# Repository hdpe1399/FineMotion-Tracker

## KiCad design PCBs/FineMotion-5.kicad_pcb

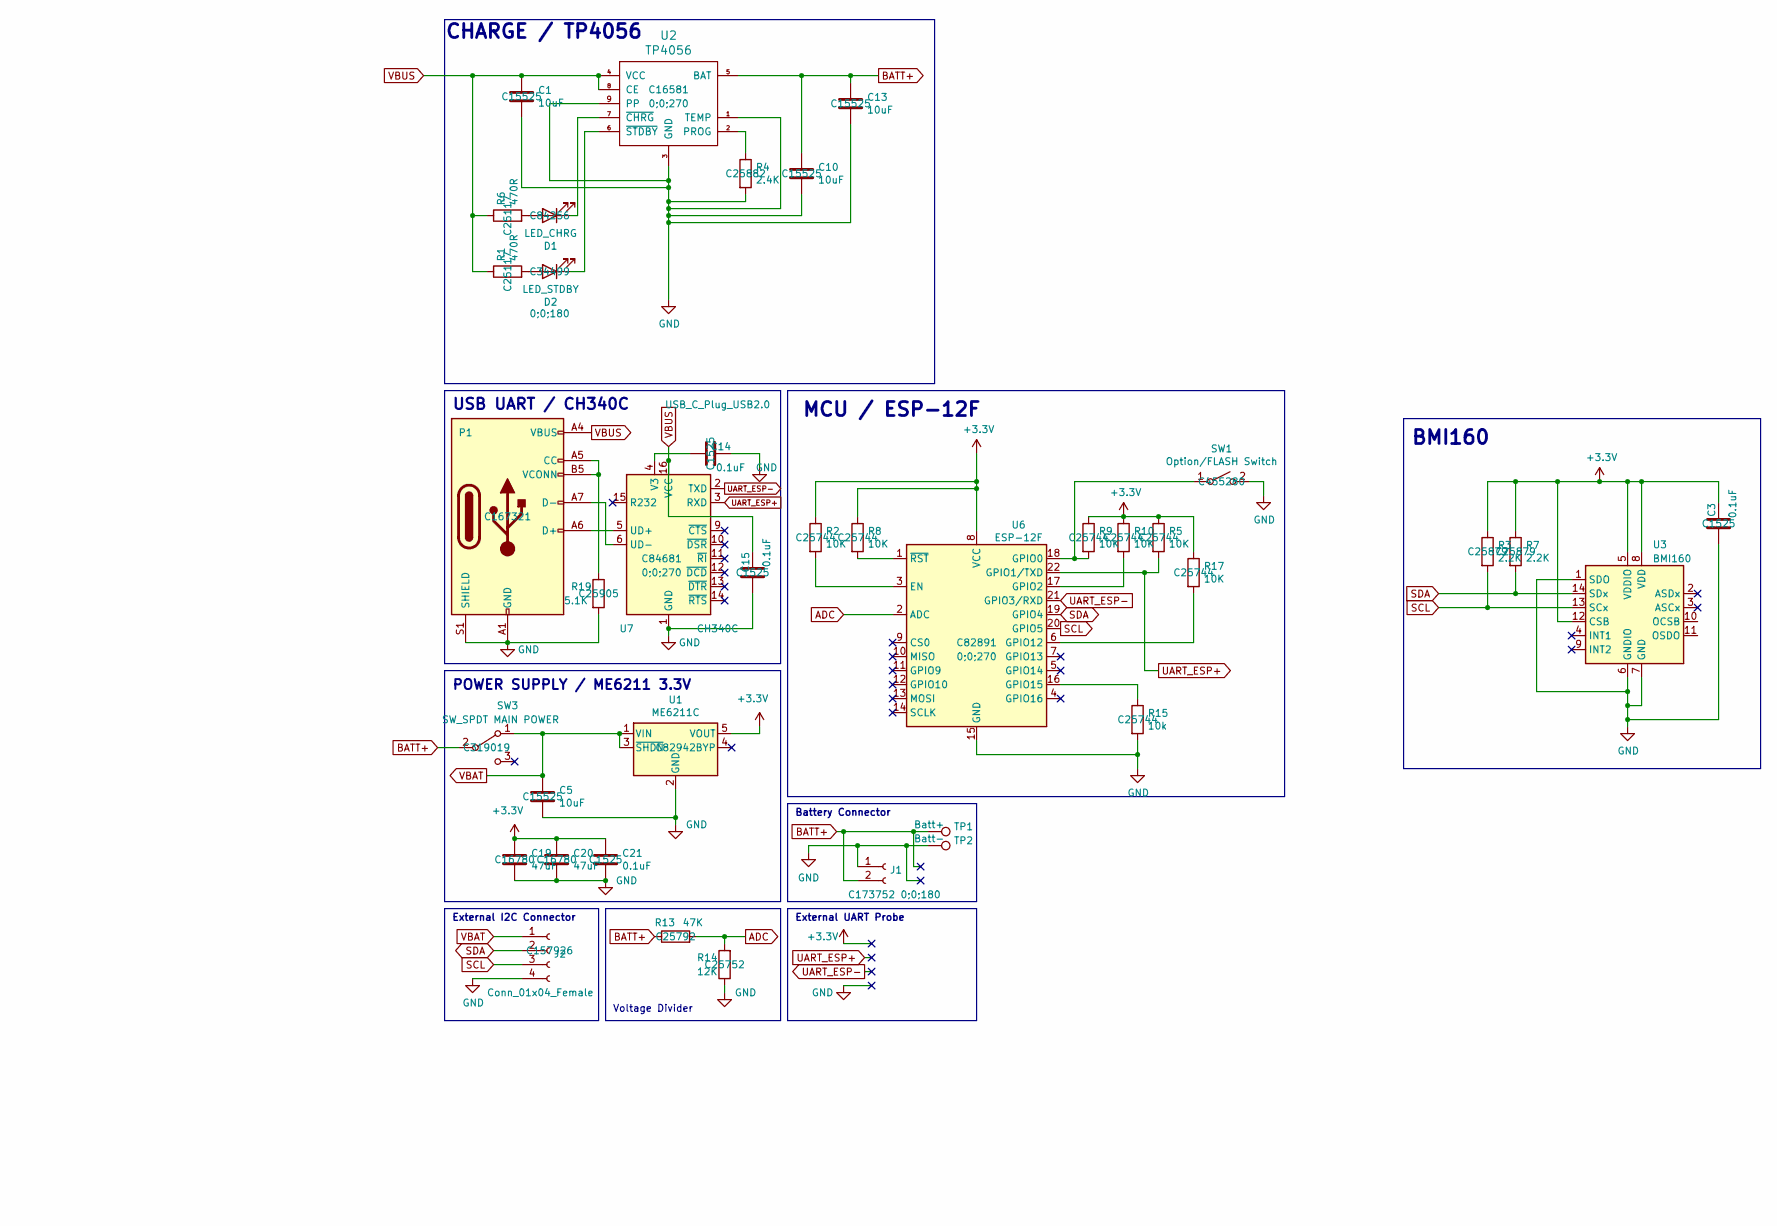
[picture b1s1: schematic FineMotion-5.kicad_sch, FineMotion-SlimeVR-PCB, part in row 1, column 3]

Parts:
C1, C5, C10, C13: 10uF; C_0402_1005Metric; LCSC C15525
C3, C14, C15, C21: 0.1uF; C_0402_1005Metric; LCSC C1525
C19, C20: 47uF; C_0805_2012Metric; LCSC C16780
D1: LED_CHRG; LED_0805_2012Metric; LCSC C84256
D2: LED_STDBY; LED_0805_2012Metric; LCSC C34499
J1: Conn_01x02_Female; JST_PH_S2B-PH-K_1x02_P2.00mm_Horizontal; LCSC C173752
J2: Conn_01x04_Female; JST_PH_S4B-PH-K_1x04_P2.00mm_Horizontal; LCSC C157926
P1: USB_C_Plug_USB2.0; USB_C_Receptacle_HRO_TYPE-C-31-M-12; LCSC C167321
R1, R6: 470R; R_0402_1005Metric; LCSC C25117
R2, R5, R8, R9, R10, R17: 10K; R_0402_1005Metric; LCSC C25744
R3, R7: 2.2K; R_0402_1005Metric; LCSC C25879
R4: 2.4K; R_0402_1005Metric; LCSC C25882
R13: 47K; R_0402_1005Metric; LCSC C25792
R14: 12K; R_0402_1005Metric; LCSC C25752
R15: 10k; R_0402_1005Metric; LCSC C25744
R19: 5.1K; R_0402_1005Metric; LCSC C25905
SW1: Option/FLASH Switch; TS-1088R; LCSC C455280
SW3: SW_SPDT MAIN POWER; SW_SPDT_PCM12; LCSC C319019
TP1: Batt+; Pin_D0.9mm_L10.0mm_W2.4mm_FlatFork
TP2: Batt-; Pin_D0.9mm_L10.0mm_W2.4mm_FlatFork
U1: ME6211C; SOT-23-5; LCSC C82942
U2: TP4056; HSOP-8-1EP_3.9x4.9mm_P1.27mm_EP2.41x3.1mm_ThermalVias; LCSC C16581
U3: BMI160; Bosch_LGA-14_3x2.5mm_P0.5mm
U6: ESP-12F; ESP-12E; LCSC C82891
U7: CH340C; SOIC-16_3.9x9.9mm_P1.27mm; LCSC C84681

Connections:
+3V3: C3.2, C19.1, C20.1, C21.1, R2.1, R3.1, R5.1, R7.1, R8.1, R9.1, R10.1, R17.1, U1.5 (VOUT), U3.5 (VDDIO), U3.8 (VDD), U3.12 (CSB), U6.8 (VCC)
ADC: R13.2, R14.2, U6.2 (ADC)
BATT+: C10.1, C13.1, J1.2, R13.1, SW3.2 (B), TP1.1, U2.5 (BAT)
GND: C1.2, C3.1, C5.2, C10.2, C13.2, C14.2, C15.1, C19.2, C20.2, C21.2, J1.1, J2.4, P1.A1 (GND), P1.A12 (GND), P1.B1 (GND), P1.B12 (GND), P1.S1 (SHIELD), R4.2, R14.1, R15.2, R19.2, SW1.2 (B), TP2.1, U1.2 (GND), U2.1 (TEMP), U2.3 (GND), U2.9 (PP), U3.1 (SDO), U3.6 (GNDIO), U3.7 (GND), U6.15 (GND), U7.1 (GND)
unnamed: D1.2 (A), R6.2
unnamed: D1.1 (K), U2.7 (~CHRG)
unnamed: D2.2 (A), R1.2
unnamed: D2.1 (K), U2.6 (~STDBY)
unnamed: P1.A5 (CC), P1.B5 (VCONN), R19.1
unnamed: P1.A6 (D+), U7.5 (UD+)
unnamed: P1.A7 (D-), U7.6 (UD-)
unnamed: R9.2, SW1.1 (A), U6.18 (GPIO0)
unnamed: R4.1, U2.2 (PROG)
unnamed: R2.2, U6.3 (EN)
unnamed: R10.2, U6.17 (GPIO2)
unnamed: R17.2, U6.6 (GPIO12)
unnamed: R15.1, U6.16 (GPIO15)
unnamed: R8.2, U6.1 (~RST)
unnamed: C14.1, U7.4 (V3)
SCL: J2.3, R3.2, U3.13 (SCx), U6.20 (GPIO5)
SDA: J2.2, R7.2, U3.14 (SDx), U6.19 (GPIO4)
UART_ESP+: R5.2, U6.22 (GPIO1/TXD), U7.3 (RXD)
UART_ESP-: U6.21 (GPIO3/RXD), U7.2 (TXD)
VBAT: C5.1, J2.1, SW3.1 (A), U1.1 (VIN), U1.3 (~SHDN)
VBUS: C1.1, C15.2, P1.A4 (VBUS), P1.A9 (VBUS), P1.B4 (VBUS), P1.B9 (VBUS), R1.1, R6.1, U2.4 (VCC), U2.8 (CE), U7.16 (VCC)

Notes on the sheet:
Voltage Divider
External UART Probe
MCU / ESP-12F
External I2C Connector
POWER SUPPLY / ME6211 3.3V
CHARGE / TP4056
BMI160
USB UART / CH340C
Battery Connector

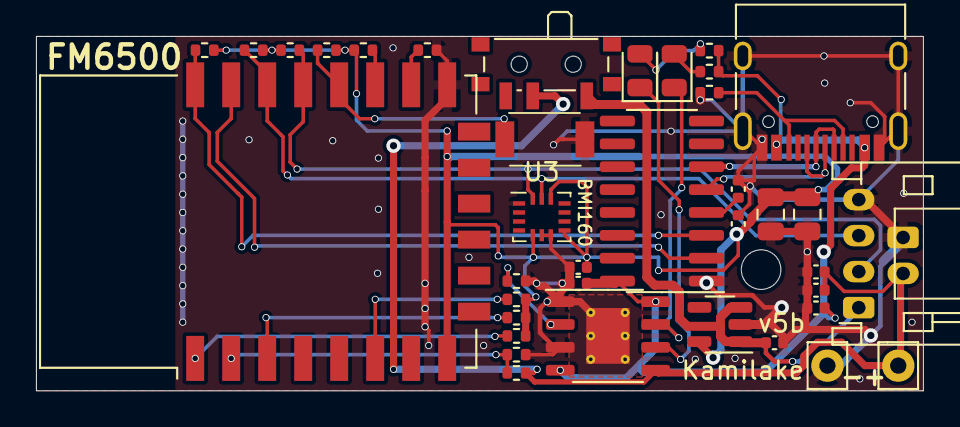
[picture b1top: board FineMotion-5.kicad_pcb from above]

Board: 2 copper layers, 49.3 x 19.7 mm, 39 parts (1 on the bottom side), 25 nets.

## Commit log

2023-03-15 bmi160

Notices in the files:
PCBs/FineMotion-5.kicad_sch:
Licensed under CERN-OHL-P v2 or later
